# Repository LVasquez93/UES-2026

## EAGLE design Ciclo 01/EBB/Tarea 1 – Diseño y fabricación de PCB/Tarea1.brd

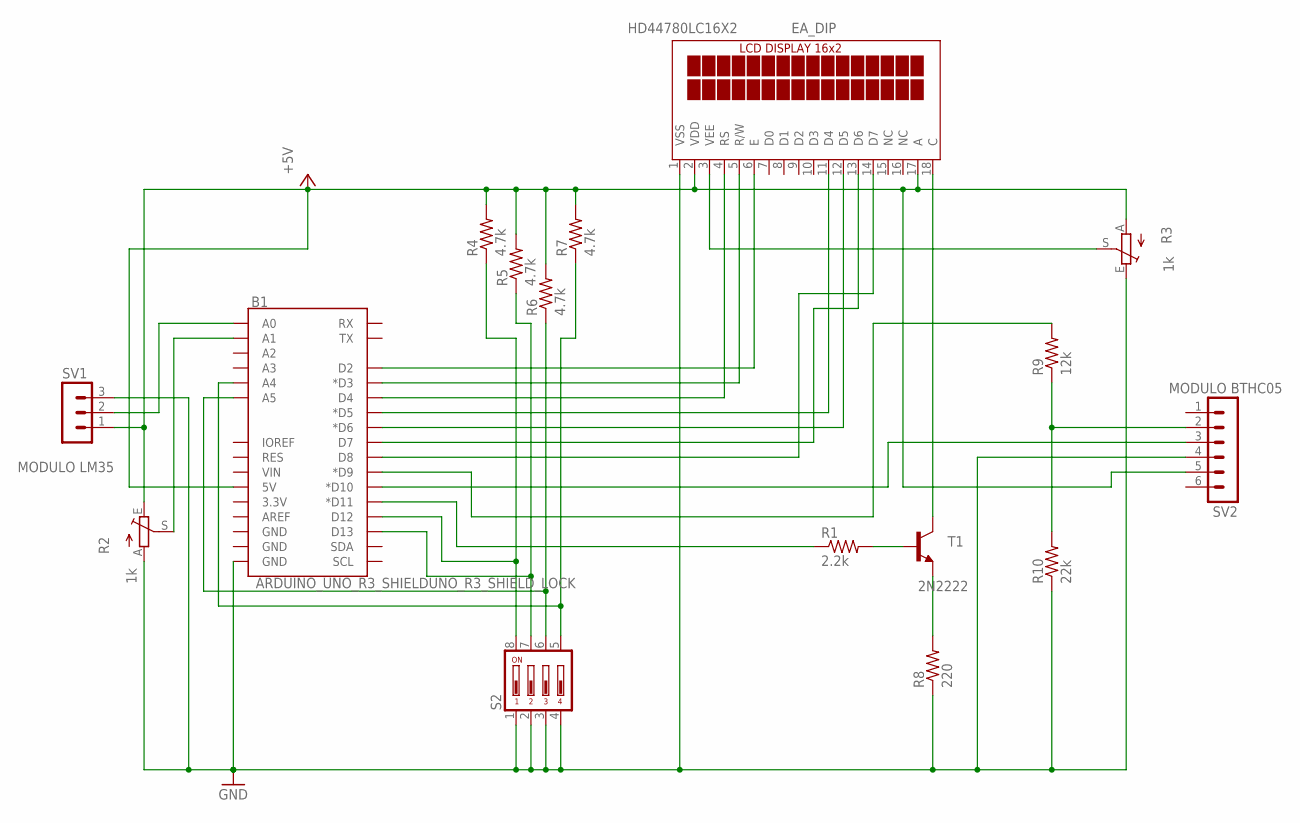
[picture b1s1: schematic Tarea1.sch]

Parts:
B1: ARDUINO_UNO_R3_SHIELDUNO_R3_SHIELD_LOCK; UNO_R3_SHIELD_LOCK
HD44780LC16X2: EA_DIP
R1: 2.2k; 0207/10
R2, R3: 1k; B25P
R4, R5, R6, R7: 4.7k; 0207/10
R8: 220; 0207/10
R9: 12k; 0207/10
R10: 22k; 0207/10
S2: SD4-04
SV1: MODULO LM35; MA03-1
SV2: MODULO BTHC05; MA06-1
T1: 2N2222; TO18

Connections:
+5V: B1.5V, HD44780LC16X2.2 (VDD), HD44780LC16X2.17 (A), R2.E, R3.A, R4.2, R5.2, R6.2, R7.2, SV1.1, SV2.5
GND: B1.GND@0 (GND), HD44780LC16X2.1 (VSS), R2.A, R3.E, R8.1, R10.1, S2.1, S2.2, S2.3, S2.4, SV1.3, SV2.4
unnamed: B1.D12, R4.1, S2.8
unnamed: B1.A1, R2.S
unnamed: B1.A0, SV1.2
unnamed: B1.D13, R5.1, S2.7
unnamed: B1.A5, R6.1, S2.6
unnamed: B1.A4, R7.1, S2.5
unnamed: R8.2, T1.1 (E)
unnamed: R1.2, T1.2 (B)
unnamed: HD44780LC16X2.18 (C), T1.3 (C)
unnamed: R9.1, R10.2, SV2.2
unnamed: HD44780LC16X2.3 (VEE), R3.S
unnamed: B1.D11 (*D11), R1.1
unnamed: B1.D9 (*D9), R9.2
unnamed: B1.D10 (*D10), SV2.3
unnamed: B1.D2, HD44780LC16X2.6 (E)
unnamed: B1.D3 (*D3), HD44780LC16X2.5 (R/W)
unnamed: B1.D4, HD44780LC16X2.4 (RS)
unnamed: B1.D5 (*D5), HD44780LC16X2.11 (D4)
unnamed: B1.D6 (*D6), HD44780LC16X2.12 (D5)
unnamed: B1.D7, HD44780LC16X2.13 (D6)
unnamed: B1.D8, HD44780LC16X2.14 (D7)

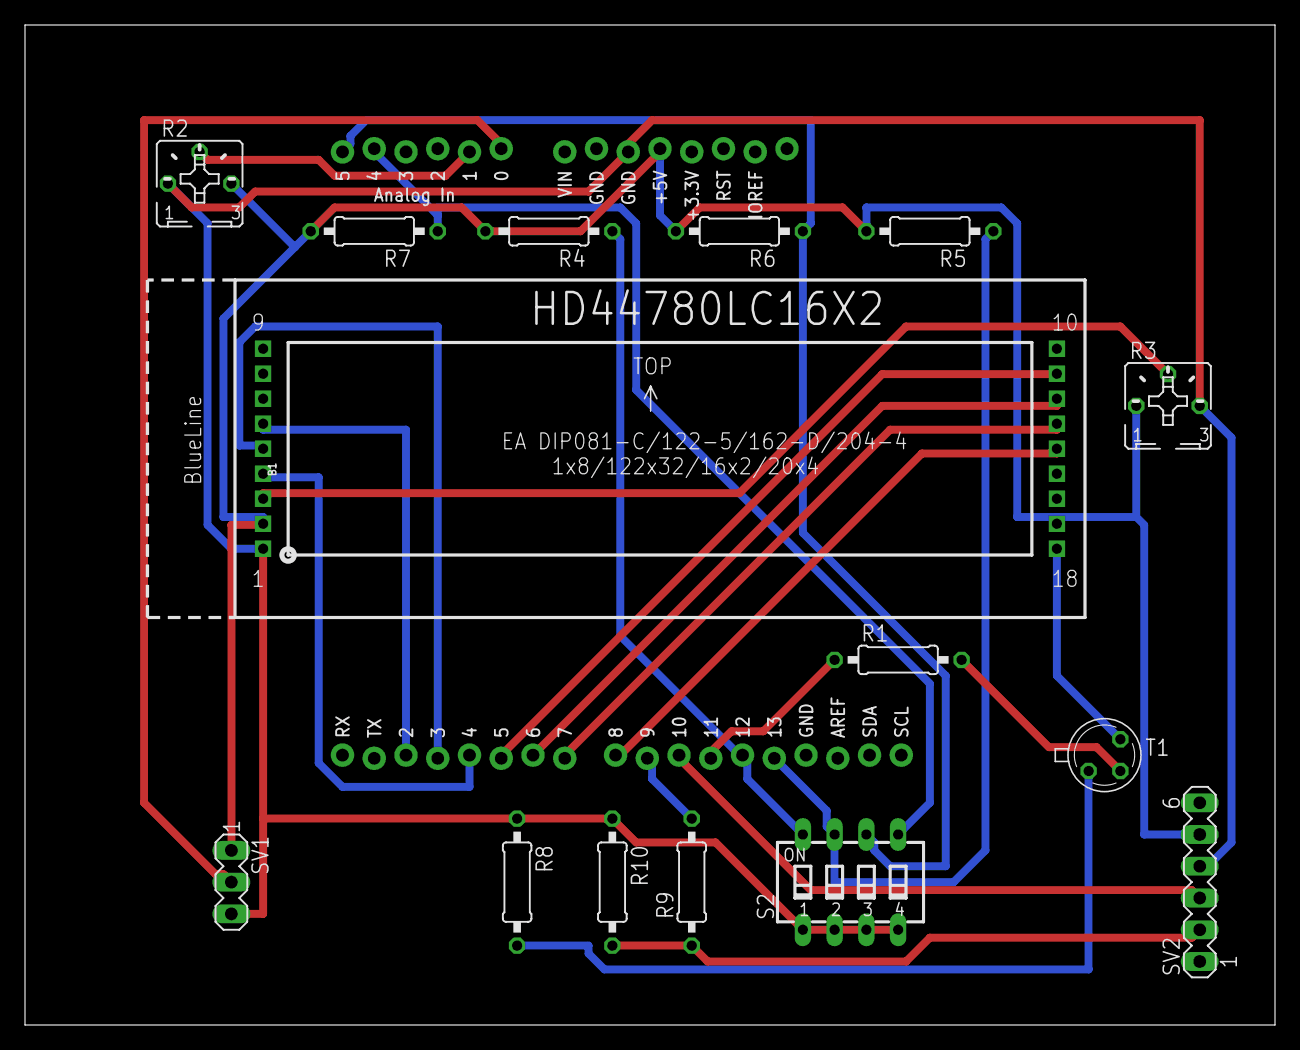
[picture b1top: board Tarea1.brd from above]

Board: 2 copper layers, 100.0 x 80.0 mm, 16 parts (0 on the bottom side), 23 nets.

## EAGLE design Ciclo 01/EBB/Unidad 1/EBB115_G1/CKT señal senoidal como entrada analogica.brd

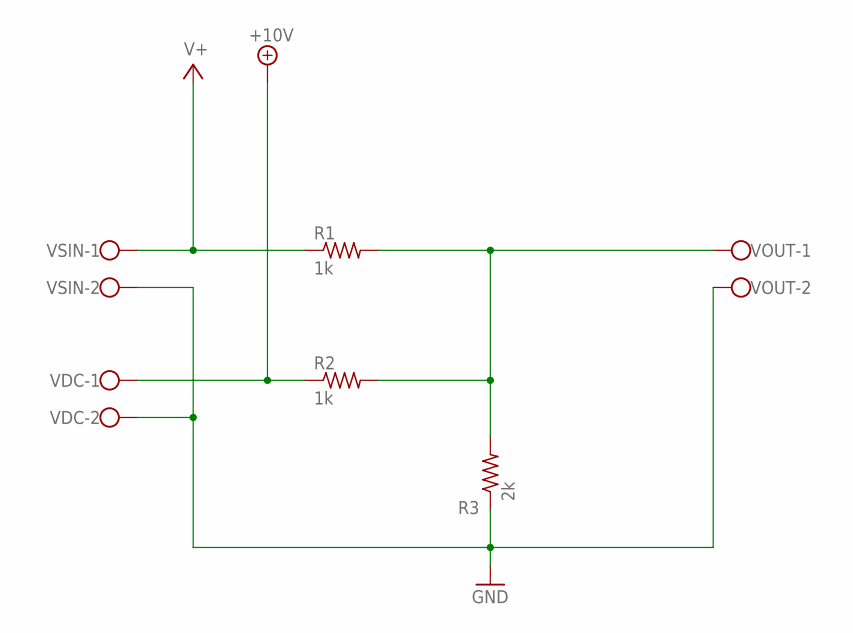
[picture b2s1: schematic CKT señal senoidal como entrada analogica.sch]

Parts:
R1, R2: 1k; 0207/10
R3: 2k; 0207/10
VDC: W237-102
VOUT: W237-102
VSIN: W237-102

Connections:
+10V: R2.1, VDC.1
GND: R3.1, VDC.2, VOUT.2, VSIN.2
unnamed: R1.2, R2.2, R3.2, VOUT.1
V+: R1.1, VSIN.1

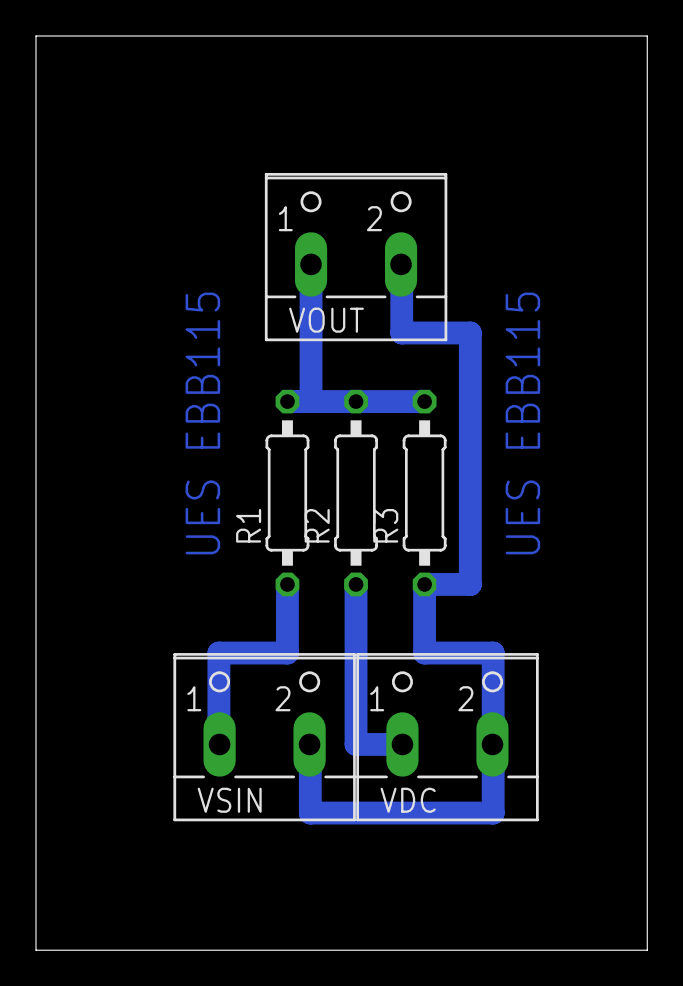
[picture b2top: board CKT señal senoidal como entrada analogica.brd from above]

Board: 2 copper layers, 34.0 x 50.8 mm, 6 parts (0 on the bottom side), 4 nets.

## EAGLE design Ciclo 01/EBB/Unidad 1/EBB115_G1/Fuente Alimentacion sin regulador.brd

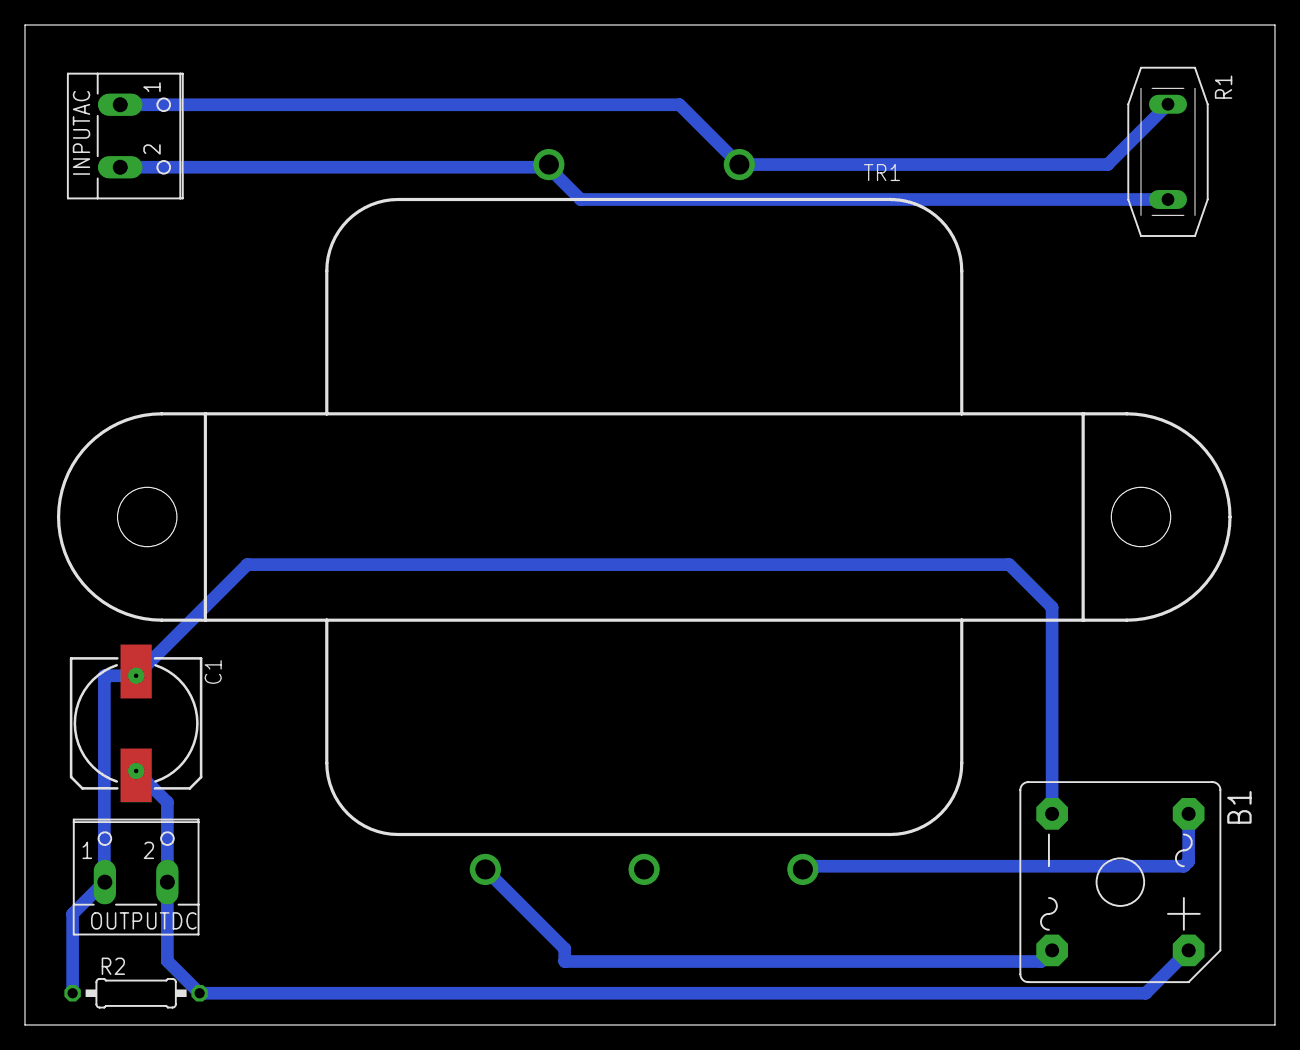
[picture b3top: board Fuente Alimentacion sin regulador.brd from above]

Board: 2 copper layers, 100.0 x 80.0 mm, 7 parts (0 on the bottom side), 6 nets.

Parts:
B1: GBPC1
C1: 153CLV-1012
INPUTAC: W237-102
OUTPUTDC: W237-102
R1: P594
R2: 0207/10
TR1: 166R5; C12H

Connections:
GNDA: B1.-, C1.-, OUTPUTDC.1, R2.1
unnamed: INPUTAC.1, R1.2, TR1.BLK@1
unnamed: INPUTAC.2, R1.1, TR1.BLK@2
unnamed: B1.AC1, TR1.GRN@1
unnamed: B1.AC2, TR1.GRN@2
unnamed: B1.+, C1.+, OUTPUTDC.2, R2.2

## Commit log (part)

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2026-02-24 Primera Carga
2026-02-25 dsdsd
2026-02-26 asasas
2026-02-27 lkjhv
2026-03-06 uyfh
2026-03-06 sasa
2026-03-06 ..,l,mlm
2026-03-08 asa123
2026-03-08 asas
2026-03-09 sdsd
2026-03-09 ñlkkl
2026-03-10 fjsaiuaifnakhfsanfsan
2026-03-16 kjvc
2026-03-17 xcxcx
2026-03-19 assssssssssssssssssss
2026-03-25 l,,,
2026-04-08 xsxsx
2026-04-09 ,mnb
2026-04-09 dsiu1full
2026-04-09 iuyfdfghjk
2026-04-10 EBB CARGA PROYECTO
2026-04-13 carga dsi unida 3.3
2026-04-14 RHU planillas y DSI U3
2026-04-24 MIP U3
2026-05-04 asasa
2026-05-05 qqqqqqq
2026-05-06 sdsdsd
2026-05-08 lkjhjkl
2026-05-10 lkmp
2026-05-11 sasas
2026-05-12 sssasas
2026-05-15 swsws
2026-05-19 zsssss
2026-05-20 qwer
2026-05-21 CRUD en proyecto DSI
2026-05-22 jbjbnmn
2026-05-26 nuevo proyecto prueba backend
2026-05-27 r564
2026-05-28 odontoloogo,citas
2026-05-28 fdsa
2026-05-28 asdfgghfds
2026-06-10 hgfd
2026-06-12 sdsds
2026-06-16 mnklñlmn
2026-06-30 lkjhjk

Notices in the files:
parts and their libraries:
SparkFun-Boards: Licensing: Creative Commons ShareAlike 4.0 International - https://creativecommons.org/licenses/by-sa/4.0
